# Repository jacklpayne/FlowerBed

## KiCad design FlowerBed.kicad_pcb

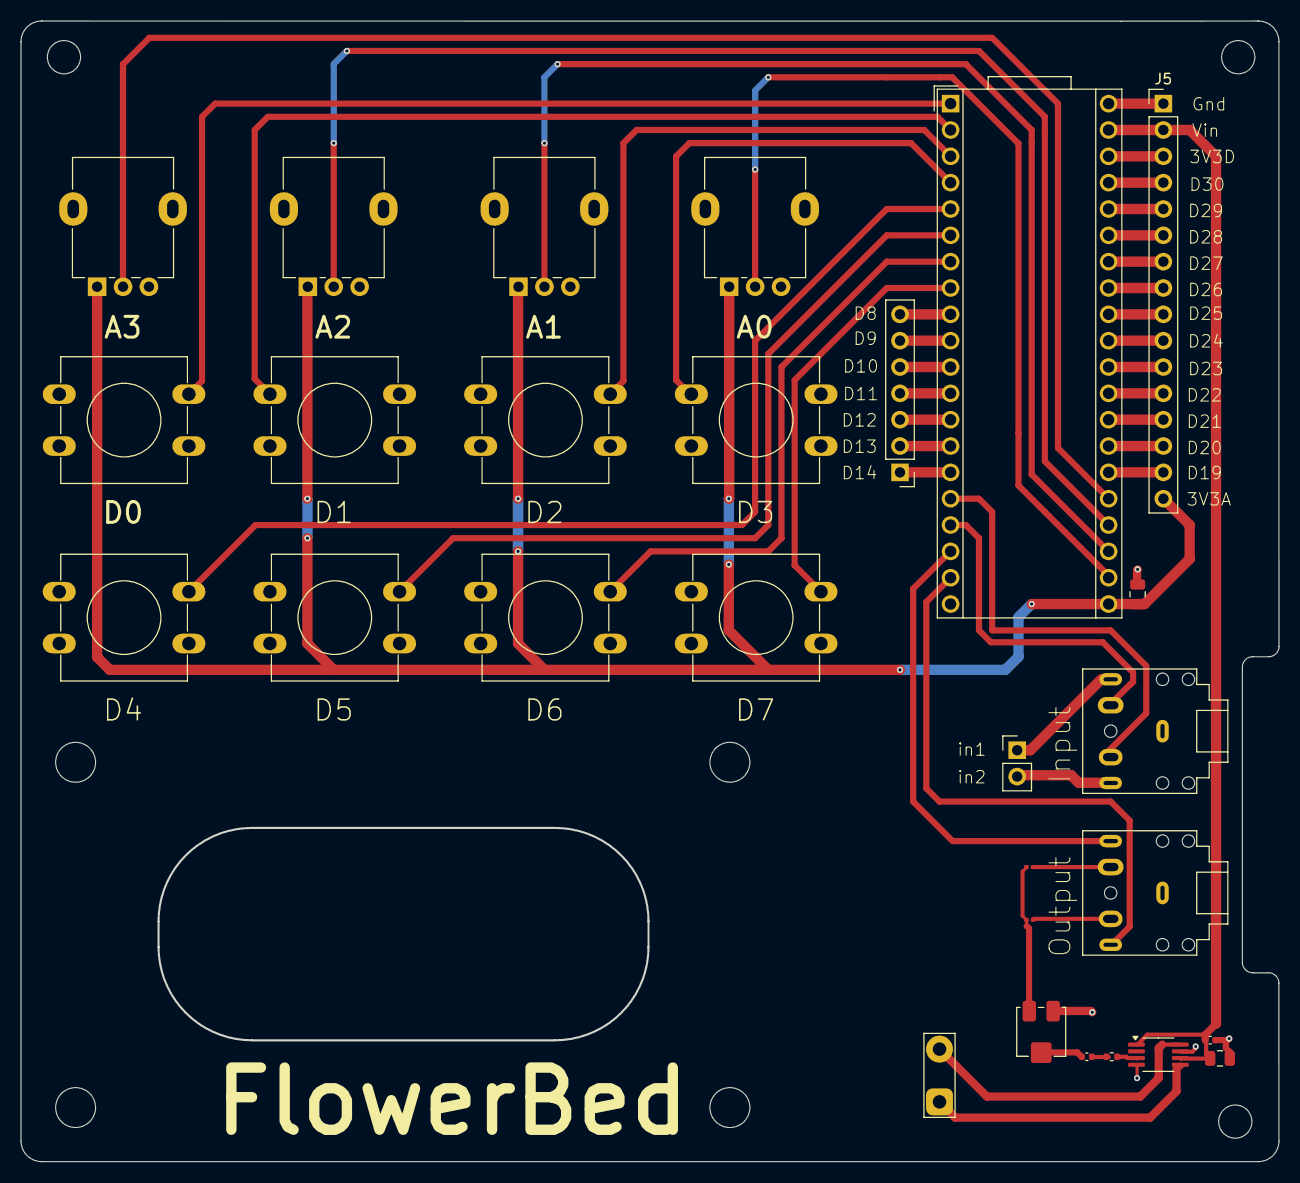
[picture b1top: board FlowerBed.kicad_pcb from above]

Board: 2 copper layers, 121.2 x 109.9 mm, 28 parts (0 on the bottom side), 49 nets.

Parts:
A1: Electrosmith_Daisy_Seed_Rev4; Electrosmith_Daisy_Seed
C1, C2: 1uF; C_0402_1005Metric
C3, C4: 47uf; C_0805_2012Metric
J1: Conn_01x02; TestPoint_2Pads_Pitch5.08mm_Drill1.3mm
J2, J3: AudioJack3_SwitchTR; Jack_3.5mm_CUI_SJ1-3525N_Horizontal
J4: Conn_01x07; PinHeader_1x07_P2.54mm_Vertical
J5: Conn_01x16; PinHeader_1x16_P2.54mm_Vertical
J6: Conn_01x02; PinHeader_1x02_P2.54mm_Vertical
POT0, POT1, POT2, POT3: R_Potentiometer_US; Potentiometer_Alpha_RD901F-40-00D_Single_Vertical
R1, R2: 1k; R_0201_0603Metric
R3: 100; R_0402_1005Metric
SW0, SW1, SW2, SW3, SW4, SW5, SW6, SW7: SW_SPST; SW_PUSH-12mm
U1: PAM8302AASCR; MSOP-8_3x3mm_P0.65mm
VR1: 10K trim; Potentiometer_Bourns_3314J_Vertical

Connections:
/3V3_A: A1.21 (3V3_A), C4.1, J5.16, POT0.1, POT1.1, POT2.1, POT3.1
/3V3_D: A1.38 (3V3_D), J5.3
/AUDIO_IN1: A1.16 (AUDIO_IN_1), J3.RN
/AUDIO_IN1_H: J3.R, J6.2
/AUDIO_IN2: A1.17 (AUDIO_IN_2), J3.TN
/AUDIO_IN2_H: J3.T, J6.1
/D0: A1.1 (USB_ID), SW0.2 (B)
/D1: A1.2 (SD_DATA_3), SW1.2 (B)
/D2: A1.3 (SD_DATA_2), SW2.2 (B)
/D3: A1.4 (SD_DATA_1), SW3.2 (B)
/D4: A1.5 (SD_DATA_0), SW4.2 (B)
/D5: A1.6 (SD_CMD), SW5.2 (B)
/D6: A1.7 (SD_CLK), SW6.2 (B)
/D7: A1.8 (SPI1_CS), SW7.2 (B)
/D8: A1.9 (SPI1_SCK), J4.7
/D9: A1.10 (SPI1_POCI), J4.6
/D10: A1.11 (SPI1_PICO), J4.5
/D11: A1.12 (I2C1_SCL), J4.4
/D12: A1.13 (I2C1_SDA), J4.3
/D13: A1.14 (USART1_TX), J4.2
/D14: A1.15 (USART1_RX), J4.1
/D15_A0: A1.22 (ADC_0), POT0.2
/D16_A1: A1.23 (ADC_1), POT1.2
/D17_A2: A1.24 (ADC_2), POT2.2
/D18_A3: A1.25 (ADC_3), POT3.2
/D19_A4: A1.26 (ADC_4), J5.15
/D20_A5: A1.27 (ADC_5), J5.14
/D21_A6: A1.28 (ADC_6), J5.13
/D22_A7: A1.29 (DAC_OUT2), J5.12
/D23_A8: A1.30 (DAC_OUT1), J5.11
/D24_A9: A1.31 (SAI2_MCLK), J5.10
/D25_A10: A1.32 (SAI2_SD_B), J5.9
/D26: A1.33 (SAI2_SD_A), J5.8
/D27: A1.34 (SAI2_FS), J5.7
/D28: A1.35 (SAI2_SCK), J5.6
/D29: A1.36 (USB_D_-), J5.5
/D30: A1.37 (USB_D_+), J5.4
/LINEOUT_L: A1.18 (AUDIO_OUT_1), J2.T
/LINEOUT_MONO: R1.2, R2.2, VR1.3 (E)
/LINEOUT_R: A1.19 (AUDIO_OUT_2), J2.R
/VO+: J1.1, U1.5 (VO_P)
/VO-: J1.2, U1.8 (VO_N)
/Vin: A1.39 (VIN), C2.1, C3.1, J5.2, U1.1 (/SD), U1.6 (VDD)
GND: A1.20 (AGND), A1.40 (DGND), C2.2, C3.2, C4.2, J2.S, J3.S, J5.1, POT0.3, POT1.3, POT2.3, POT3.3, SW0.1 (A), SW1.1 (A), SW1.2 (B), SW2.1 (A), SW3.1 (A), SW3.2 (B), SW4.1 (A), SW5.1 (A), SW6.1 (A), SW7.1 (A), U1.4 (IN_N), U1.7 (GND), VR1.1 (A)
unnamed: C1.1, R3.1
unnamed: J2.RN, R1.1
unnamed: J2.TN, R2.1
unnamed: R3.2, U1.3 (IN_P)
unnamed: C1.2, VR1.2 (S)

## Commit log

2026-05-06 Init
2026-05-06 Begins alternate layout with pots above switches
2026-05-06 Finishes GPIO routing
2026-05-11 Legacy active sum
2026-05-14 Make sum passive, add manuals
2026-05-14 Move outputs & fab files
2026-05-14 Update footprints for ICs
2026-05-15 Update footprints for passives
